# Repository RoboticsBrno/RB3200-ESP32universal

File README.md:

# RB3200 - ESP32 universal board

The ESP32 board you have always dreamed of by RobotikaBrno.cz!

## Features

- 4 pin headers for each of the ESP32-WROOM-32 pins
    - pin headers closest to the ESP32 module are directly exposed from the
      module
    - pin headers further from the module are protected by a serial 180R
      resistor - so you can attach e.g. a LED directly or you don't have to
      worry if you accidentally switch you grounded input to output.
    - each pin has its own 5V, 3V3 and GND pin
- Arduino Uno compatible headerincluded
- USB2Serial chip for easy button-less programming
- support for an external power supply with high-current voltage regulator
- diagnostic LEDs

## Populated board

## Manufacturing

There are pre-exported gerber files in the `gerbers` directory. This directory
is always up-to-date for every release (the master branch). There is also the
`bom.tsv` file which contains BOM with order codes for Farnell, TS, Mouser and
DigiKey. Note that the current development branch (`vX.Y`) does not guarantee
up-to-date gerber and BOM files.

As our board features many pin headers and you might not want to populate them
all, we did **not** include them in the BOM. Keep that please in mind when
ordering the components.

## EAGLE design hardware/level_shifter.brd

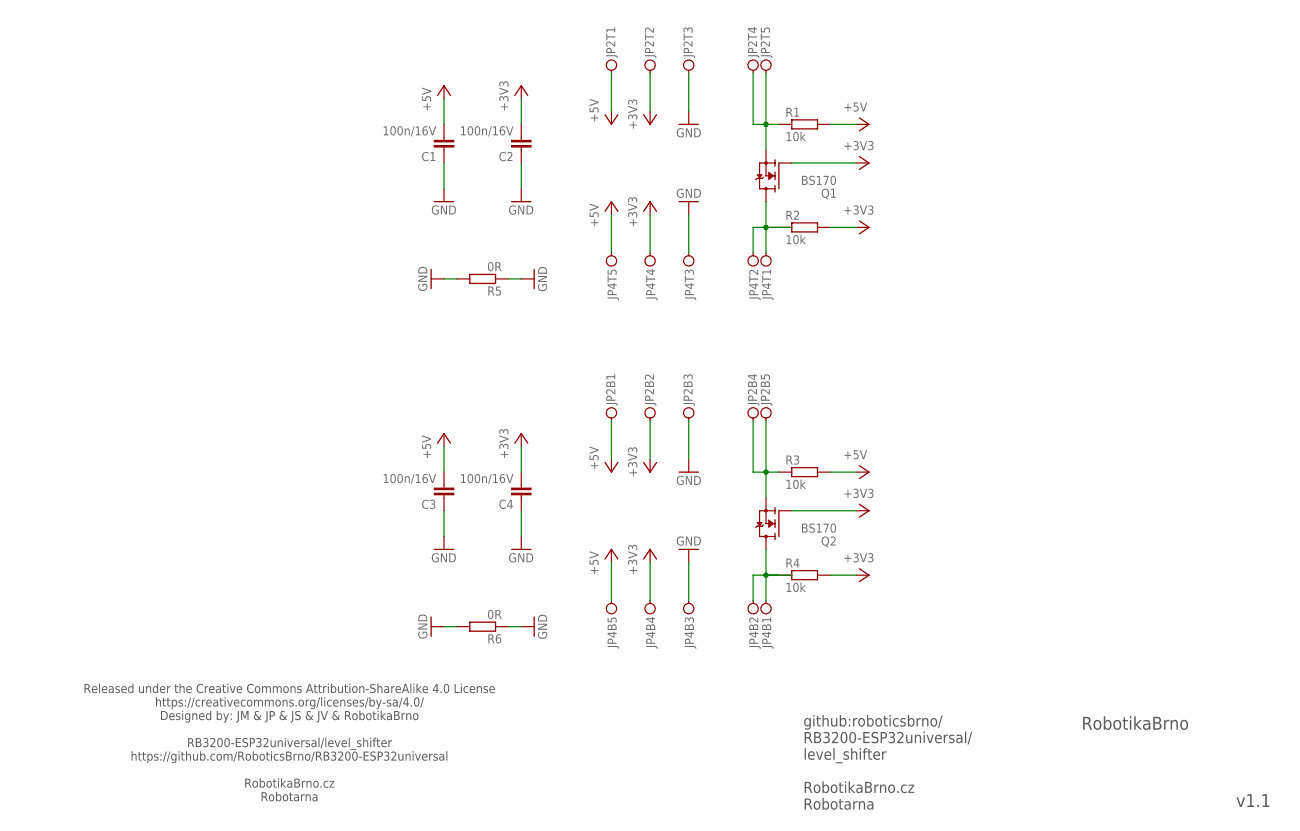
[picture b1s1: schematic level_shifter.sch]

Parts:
C1, C2, C3, C4: 100n/16V; C0603S
JP2, JP4: PINH2X05; PINH2X05SMD
Q1: BS170; SOT23_DIST
Q2: BS170; SOT23
R1, R2, R3, R4: 10k; R0603S
R5, R6: 0R; R1206S

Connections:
+3V3: C2.2, C4.2, JP2.B2, JP2.T2, JP4.B4, JP4.T4, Q1.1 (G), Q2.1 (G), R2.2, R4.2
+5V: C1.2, C3.2, JP2.B1, JP2.T1, JP4.B5, JP4.T5, R1.2, R3.2
GND: C1.1, C2.1, C3.1, C4.1, JP2.B3, JP2.T3, JP4.B3, JP4.T3, R5.1, R5.2, R6.1, R6.2
IN_B: JP4.B1, JP4.B2, Q2.3 (D), R4.1
IN_T: JP4.T1, JP4.T2, Q1.3 (D), R2.1
OUT_B: JP2.B4, JP2.B5, Q2.2 (S), R3.1
OUT_T: JP2.T4, JP2.T5, Q1.2 (S), R1.1

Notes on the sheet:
github:roboticsbrno/ RB3200-ESP32universal/ level_shifter RobotikaBrno.cz Robotarna
Released under the Creative Commons Attribution-ShareAlike 4.0 License https://creativecommons.org/licenses/by-sa/4.0/ Designed by: JM & JP & JS & JV & RobotikaBrno RB3200-ESP32universal/level_shifter https://github.com/RoboticsBrno/RB3200-ESP32universal RobotikaBrno.cz Robotarna
RobotikaBrno
v1.1

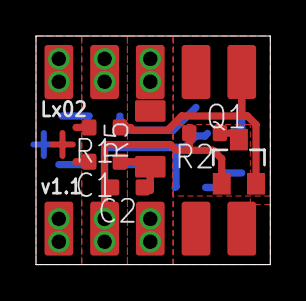
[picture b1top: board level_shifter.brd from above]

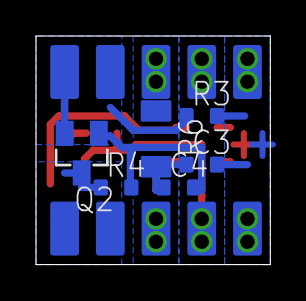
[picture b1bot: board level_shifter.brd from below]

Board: 2 copper layers, 13.0 x 12.7 mm, 14 parts (6 on the bottom side), 7 nets.

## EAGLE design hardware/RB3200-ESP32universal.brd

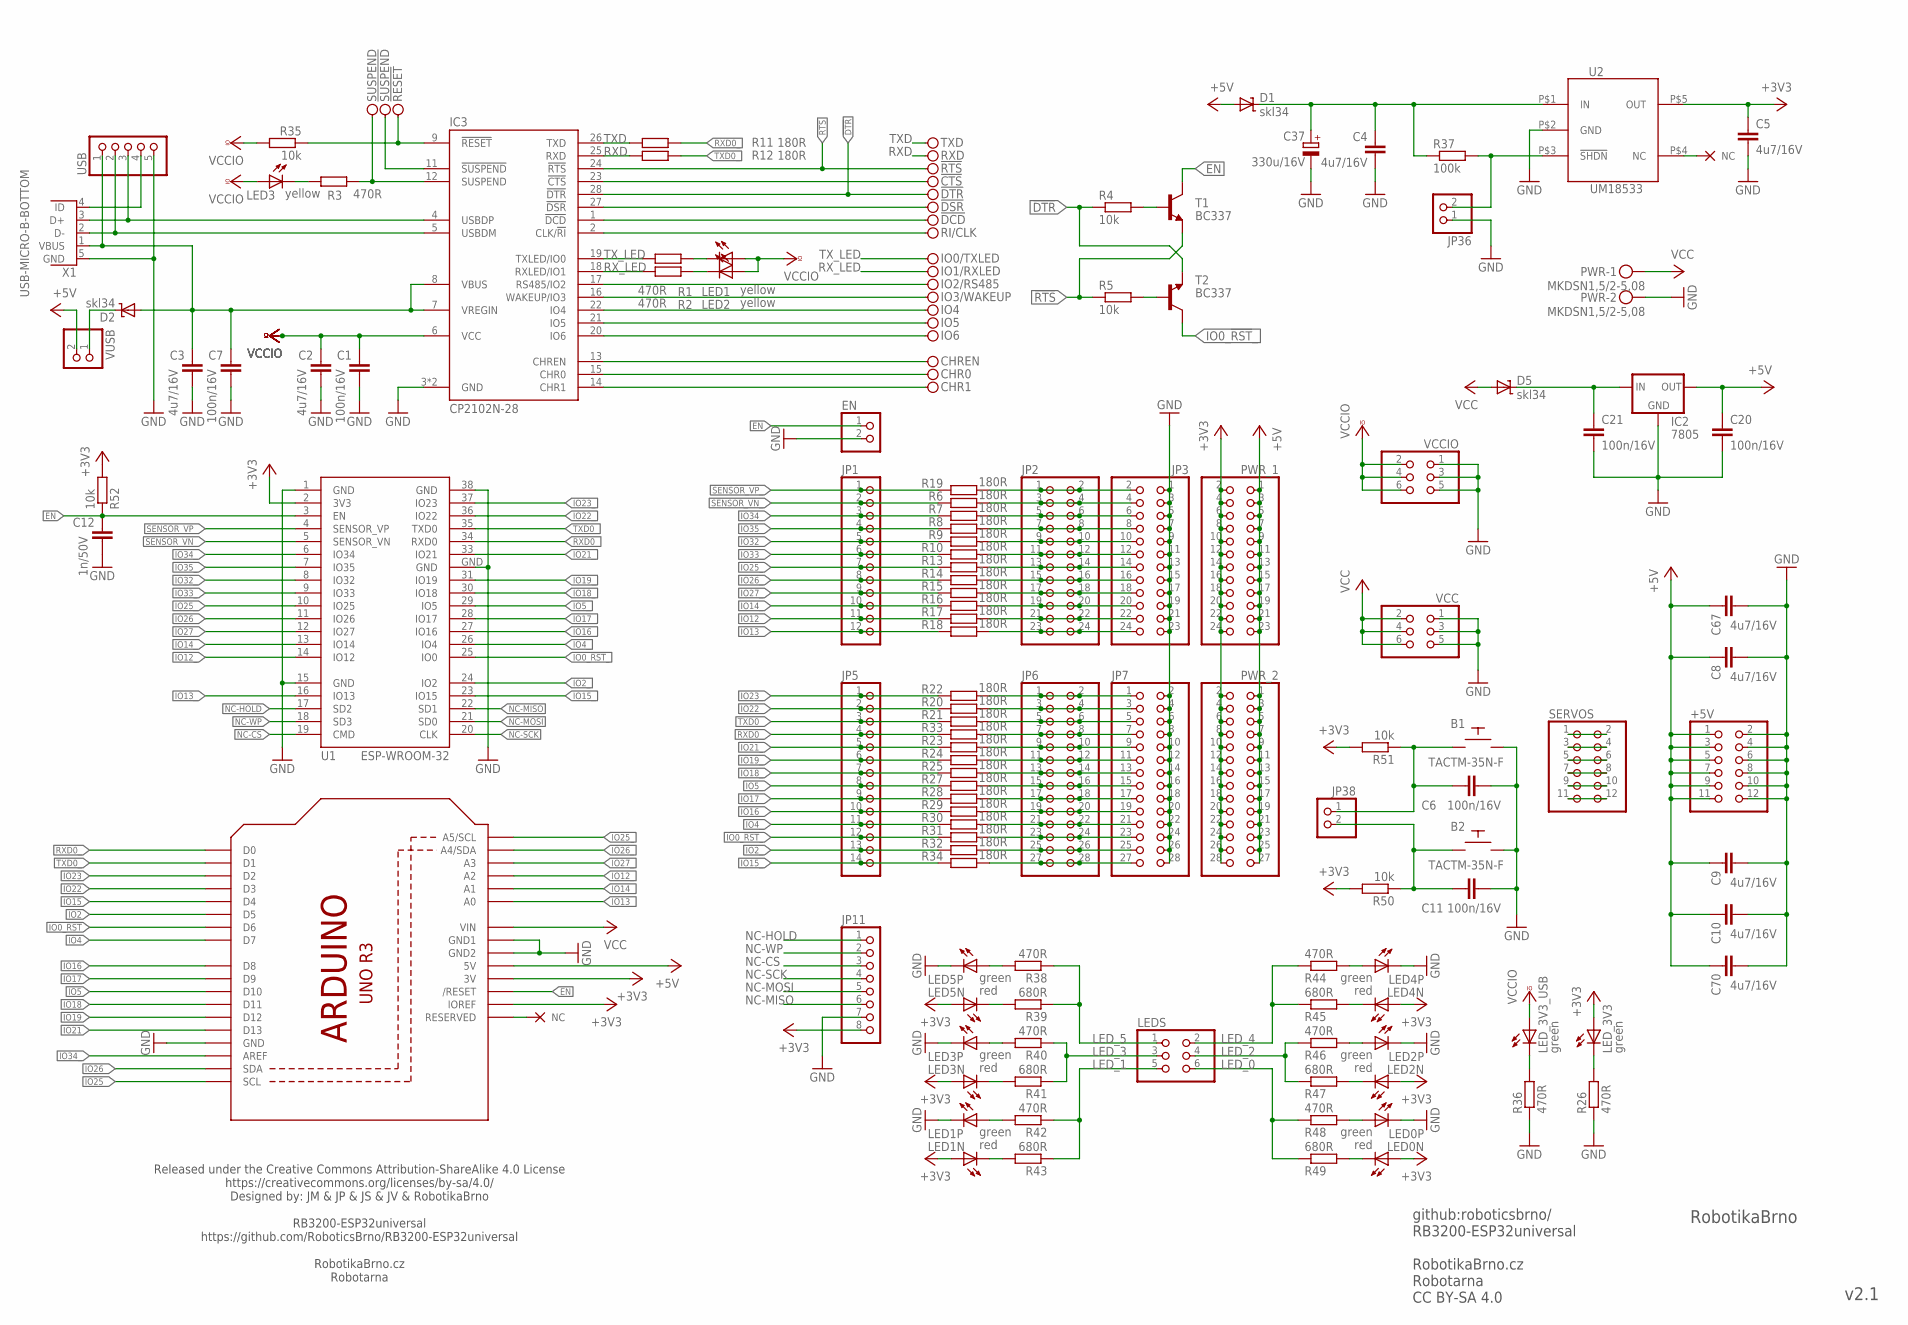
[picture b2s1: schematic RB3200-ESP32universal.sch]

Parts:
!CTS: PINH1X01; 1X01; DIGIKEY WM14724-ND
!DCD: PINH1X01; 1X01; DIGIKEY WM14724-ND
!DSR: PINH1X01; 1X01; DIGIKEY WM14724-ND
!DTR: PINH1X01; 1X01; DIGIKEY WM14724-ND
!RESET: PINH1X01; 1X01; DIGIKEY WM14724-ND
!RTS: PINH1X01; 1X01; DIGIKEY WM14724-ND
!SUSPEND: PINH1X01; 1X01; DIGIKEY WM14724-ND
+5V: PINHD-2X6; 2X06; DIGIKEY A122662-ND
B1, B2: TACTM-35N-F; DIGIKEY CKN1574TR-ND
C1, C6, C7, C11, C20, C21: 100n/16V; C0402; DIGIKEY 732-7478-1-ND
C2, C3, C4, C5: 4u7/16V; C0603; DIGIKEY 478-1253-1-ND
C8, C9, C10, C67, C70: 4u7/16V; C0805; DIGIKEY 1276-2970-1-ND
C12: 1n/50V; C0603; DIGIKEY 399-1082-1-ND
C37: 330u/16V; E5-10,5; DIGIKEY 493-6629-1-ND
CHR0, CHR1: PINH1X01; 1X01; DIGIKEY WM14724-ND
CHREN: PINH1X01; 1X01; DIGIKEY WM14724-ND
D1, D2, D5: skl34; SOD123
EN: PINHD-1X2; 1X02; DIGIKEY 3M9457-02-ND
IC2: 7805; 78XXS; DIGIKEY 1016-1538-5-ND
IC3: CP2102N-28; QFN28-PAD; MPN CP2102; DIGIKEY 336-3694-ND
IO0/TXLED, IO1/RXLED, IO2/RS485, IO3/WAKEUP, IO4, IO5, IO6: PINH1X01; 1X01; DIGIKEY WM14724-ND
JP1: PINHD-1X12; 1X12; DIGIKEY WM50014-12-ND
JP2, JP3: PINHD-2X12; 2X12; DIGIKEY WM8148-ND
JP5: PINHD-1X14; 1X14; FARNELL 2356164
JP6, JP7: PINHD-2X14; 2X14; DIGIKEY WM8150-ND
JP11: PINHD-1X8; 1X08; DIGIKEY A122911-ND
JP36, JP38: PINHD-1X2; 1X02; DIGIKEY 3M9457-02-ND
LED0N, LED1N, LED2N, LED3N, LED4N, LED5N: red; CHIPLED_0603; DIGIKEY 160-1447-1-ND
LED0P, LED1P, LED2P, LED3P, LED4P, LED5P: green; CHIPLED_0603; DIGIKEY 160-1446-1-ND
LED1, LED2, LED3: yellow; CHIP-LED0603; DIGIKEY 732-4981-1-ND
LEDS: PINHD-2X3; 2X03; DIGIKEY A122915-ND
LED_3V3, LED_3V3_USB: green; CHIPLED_0603; DIGIKEY 160-1446-1-ND
PWR: MKDSN1,5/2-5,08; DIGIKEY 277-5953-ND
PWR_1: PINHD-2X12; 2X12; DIGIKEY WM8148-ND
PWR_2: PINHD-2X14; 2X14; DIGIKEY WM8150-ND
R1, R2, R3, R26, R36, R38, R40, R42, R44, R46, R48: 470R; R0603; DIGIKEY 311-470HRCT-ND
R4, R5, R35, R50, R51, R52: 10k; R0603; DIGIKEY 311-10KGRCT-ND
R6, R7, R8, R9, R10, R11, R12, R13, R14, R15, R16, R17, R18, R19, R20, R21, R22, R23, R24, R25, R27, R28, R29, R30, R31, R32, R33, R34: 180R; R0603; DIGIKEY 311-180HRCT-ND
R37: 100k; R0603; DIGIKEY 311-100KHRCT-ND
R39, R41, R43, R45, R47, R49: 680R; R0603; DIGIKEY 311-680HRCT-ND
RI/CLK: PINH1X01; 1X01; DIGIKEY WM14724-ND
RXD: PINH1X01; 1X01; DIGIKEY WM14724-ND
SERVOS: PINHD-2X6; 2X06; DIGIKEY A122662-ND
SUSPEND: PINH1X01; 1X01; DIGIKEY WM14724-ND
T1, T2: BC337; SOT23; DIGIKEY 1727-2919-1-ND
TXD: PINH1X01; 1X01; DIGIKEY WM14724-ND
U1: ESP-WROOM-32; MPN ESP32-WROMM-32; DIGIKEY 1738-1294-ND
U2: UM18533; SOT23-5; MPN TPS73033DBVT; DIGIKEY 296-17580-1-ND
U3: ARDUINOR3-BPLACE
USB: PINHD-1X5; 1X05; DIGIKEY 732-5318-ND
VCC: PINHD-2X3; 2X03; DIGIKEY A122915-ND
VCCIO: PINHD-2X3; 2X03; DIGIKEY A122915-ND
VUSB: PINHD-1X2; 1X02; DIGIKEY 3M9457-02-ND
X1: USB-MICRO-B-BOTTOM; USB-MICRO-B-BOTTOM-MOLEX; DIGIKEY WM17141CT-ND

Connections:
3V3_IN: C4.1, C37.+, D1.C, R37.1, U2.P$1 (IN)
5V_USB: D2.C, VUSB.1
!DTR: !DTR.1, IC3.28 (!DTR), R4.1, T2.2 (E)
!DTR_B: R4.2, T1.1 (B)
!RESET: !RESET.1, IC3.9 (!RESET), R35.1
!RTS: !RTS.1, IC3.24 (!RTS), R5.1, T1.2 (E)
!RTS_B: R5.2, T2.1 (B)
!SHDN: JP36.2, R37.2, U2.P$3 (!SHDN)
!SUSPEND: !SUSPEND.1, IC3.11 (!SUSPEND)
+3V3: C5.1, JP11.8, LED0N.A, LED1N.A, LED2N.A, LED3N.A, LED4N.A, LED5N.A, LED_3V3.A, PWR_1.2, PWR_1.4, PWR_1.6, PWR_1.8, PWR_1.10, PWR_1.12, PWR_1.14, PWR_1.16, PWR_1.18, PWR_1.20, PWR_1.22, PWR_1.24, PWR_2.2, PWR_2.4, PWR_2.6, PWR_2.8, PWR_2.10, PWR_2.12, PWR_2.14, PWR_2.16, PWR_2.18, PWR_2.20, PWR_2.22, PWR_2.24, PWR_2.26, PWR_2.28, R50.2, R51.2, R52.2, U1.2 (3V3), U2.P$5 (OUT), U3.3V, U3.IOREF
+5V: +5V.1, +5V.3, +5V.5, +5V.7, +5V.9, +5V.11, C8.1, C9.1, C10.1, C20.1, C67.1, C70.1, D1.A, IC2.OUT, PWR_1.1, PWR_1.3, PWR_1.5, PWR_1.7, PWR_1.9, PWR_1.11, PWR_1.13, PWR_1.15, PWR_1.17, PWR_1.19, PWR_1.21, PWR_1.23, PWR_2.1, PWR_2.3, PWR_2.5, PWR_2.7, PWR_2.9, PWR_2.11, PWR_2.13, PWR_2.15, PWR_2.17, PWR_2.19, PWR_2.21, PWR_2.23, PWR_2.25, PWR_2.27, U3.5V, VUSB.2
BTN0: B1.P$4, C6.2, JP38.1, R51.1
BTN1: B2.P$4, C11.2, JP38.2, R50.1
CHR0: CHR0.1, IC3.15 (CHR0)
CHR1: CHR1.1, IC3.14 (CHR1)
CHREN: CHREN.1, IC3.13 (CHREN)
CLK/!RI: IC3.2 (CLK/!RI), RI/CLK.1
DCD: !DCD.1, IC3.1 (!DCD)
DM: IC3.5 (USBDM), USB.2, X1.2 (D-)
DP: IC3.4 (USBDP), USB.3, X1.3 (D+)
DSR: !DSR.1, IC3.27 (!DSR)
EN: C12.1, EN.1, R52.1, T1.3 (C), U1.3 (EN), U3.RESET (/RESET)
GND: +5V.2, +5V.4, +5V.6, +5V.8, +5V.10, +5V.12, B1.P$2, B2.P$2, C1.2, C2.2, C3.2, C4.2, C5.2, C6.1, C7.2, C8.2, C9.2, C10.2, C11.1, C12.2, C20.2, C21.2, C37.-, C67.2, C70.2, EN.2, IC2.GND, IC3.3 (GND), IC3.PAD (GND), JP3.1, JP3.3, JP3.5, JP3.7, JP3.9, JP3.11, JP3.13, JP3.15, JP3.17, JP3.19, JP3.21, JP3.23, JP7.2, JP7.4, JP7.6, JP7.8, JP7.10, JP7.12, JP7.14, JP7.16, JP7.18, JP7.20, JP7.22, JP7.24, JP7.26, JP7.28, JP11.7, JP36.1, LED0P.C, LED1P.C, LED2P.C, LED3P.C, LED4P.C, LED5P.C, PWR.2, R26.1, R36.1, U1.1 (GND), U1.15 (GND), U1.38 (GND), U1.GND, U2.P$2 (GND), U3.GND, U3.GND1, U3.GND2, USB.5, VCC.1, VCC.3, VCC.5, VCCIO.1, VCCIO.3, VCCIO.5, X1.5 (GND)
IO0_!RST: JP6.23, JP6.24, JP7.23, R31.1, U3.D6
IO0_!RST!_: JP5.12, R31.2, T2.3 (C), U1.25 (IO0)
IO2: JP6.25, JP6.26, JP7.25, R32.1, U3.D5
IO2_: JP5.13, R32.2, U1.24 (IO2)
IO4: JP6.21, JP6.22, JP7.21, R30.1, U3.D7
IO4_: JP5.11, R30.2, U1.26 (IO4)
IO5: JP6.15, JP6.16, JP7.15, R27.1, U3.D10
IO5_: JP5.8, R27.2, U1.29 (IO5)
IO12: JP2.21, JP2.22, JP3.22, R17.1
IO12_: JP1.11, R17.2, U1.14 (IO12), U3.A2
IO13: JP2.23, JP2.24, JP3.24, R18.1
IO13_: JP1.12, R18.2, U1.16 (IO13), U3.A0
IO14: JP2.19, JP2.20, JP3.20, R16.1
IO14_: JP1.10, R16.2, U1.13 (IO14), U3.A1
IO15: JP6.27, JP6.28, JP7.27, R34.1, U3.D4
IO15_: JP5.14, R34.2, U1.23 (IO15)
IO16: JP6.19, JP6.20, JP7.19, R29.1, U3.D8
IO16_: JP5.10, R29.2, U1.27 (IO16)
IO17: JP6.17, JP6.18, JP7.17, R28.1, U3.D9
IO17_: JP5.9, R28.2, U1.28 (IO17)
IO18: JP6.13, JP6.14, JP7.13, R25.1, U3.D11
IO18_: JP5.7, R25.2, U1.30 (IO18)
IO19: JP6.11, JP6.12, JP7.11, R24.1, U3.D12
IO19_: JP5.6, R24.2, U1.31 (IO19)
IO21: JP6.9, JP6.10, JP7.9, R23.1, U3.D13
IO21_: JP5.5, R23.2, U1.33 (IO21)
IO22: JP6.3, JP6.4, JP7.3, R20.1, U3.D3
IO22_: JP5.2, R20.2, U1.36 (IO22)
IO23: JP6.1, JP6.2, JP7.1, R22.1, U3.D2
IO23_: JP5.1, R22.2, U1.37 (IO23)
IO25: JP2.13, JP2.14, JP3.14, R13.1
IO25_: JP1.7, R13.2, U1.10 (IO25), U3.A5 (A5/SCL), U3.SCL
IO26: JP2.15, JP2.16, JP3.16, R14.1
IO26_: JP1.8, R14.2, U1.11 (IO26), U3.A4 (A4/SDA), U3.SDA
IO27: JP2.17, JP2.18, JP3.18, R15.1
IO27_: JP1.9, R15.2, U1.12 (IO27), U3.A3
IO32: JP2.9, JP2.10, JP3.10, R9.1
IO32_: JP1.5, R9.2, U1.8 (IO32)
IO33: JP2.11, JP2.12, JP3.12, R10.1
IO33_: JP1.6, R10.2, U1.9 (IO33)
IO34: JP2.5, JP2.6, JP3.6, R7.1
IO34_: JP1.3, R7.2, U1.6 (IO34), U3.AREF
IO35: JP2.7, JP2.8, JP3.8, R8.1
IO35_: JP1.4, R8.2, U1.7 (IO35)
LED0N: LED0N.C, R49.2
LED0P: LED0P.A, R48.2
LED1N: LED1N.C, R43.2
LED1P: LED1P.A, R42.2
LED2N: LED2N.C, R47.2
LED2P: LED2P.A, R46.2
LED3N: LED3N.C, R41.2
LED3P: LED3P.A, R40.2
LED4N: LED4N.C, R45.2
LED4P: LED4P.A, R44.2
LED5N: LED5N.C, R39.2
LED5P: LED5P.A, R38.2
LED_0: LEDS.6, R48.1, R49.1
LED_1: LEDS.5, R42.1, R43.1
LED_2: LEDS.4, R46.1, R47.1
LED_3: LEDS.3, R40.1, R41.1
LED_3V3: LED_3V3.C, R26.2
LED_3V3_USB: LED_3V3_USB.C, R36.2
LED_4: LEDS.2, R44.1, R45.1
LED_5: LEDS.1, R38.1, R39.1
unnamed: !CTS.1, IC3.23 (!CTS)
unnamed: LED3.C, R3.2
unnamed: SERVOS.1, SERVOS.2
unnamed: SERVOS.3, SERVOS.4
unnamed: SERVOS.5, SERVOS.6
unnamed: SERVOS.7, SERVOS.8
unnamed: SERVOS.9, SERVOS.10
unnamed: SERVOS.11, SERVOS.12
NC-CS: JP11.3, U1.19 (CMD)
NC-HOLD: JP11.1, U1.17 (SD2)
NC-MISO: JP11.6, U1.22 (SD1)
NC-MOSI: JP11.5, U1.21 (SD0)
NC-SCK: JP11.4, U1.20 (CLK)
NC-WP: JP11.2, U1.18 (SD3)
RX-LED: LED2.C, R2.1
RXD: IC3.25 (RXD), R12.1, RXD.1
RXD0: JP6.7, JP6.8, JP7.7, R33.1, U3.D0
RXD0_: JP5.4, R11.2, R33.2, U1.34 (RXD0)
RX_LED: IC3.18 (RXLED/IO1), IO1/RXLED.1, R2.2
SENSOR_VN: JP2.3, JP2.4, JP3.4, R6.1
SENSOR_VN_: JP1.2, R6.2, U1.5 (SENSOR_VN)
SENSOR_VP: JP2.1, JP2.2, JP3.2, R19.1
SENSOR_VP_: JP1.1, R19.2, U1.4 (SENSOR_VP)
SUSPEND: IC3.12 (SUSPEND), R3.1, SUSPEND.1
TX-LED: LED1.C, R1.1
TXD: IC3.26 (TXD), R11.1, TXD.1
TXD0: JP6.5, JP6.6, JP7.5, R21.1, U3.D1
TXD0_: JP5.3, R12.2, R21.2, U1.35 (TXD0)
TX_LED: IC3.19 (TXLED/IO0), IO0/TXLED.1, R1.2
U2_NC: U2.P$4 (NC)
USBID: USB.4, X1.4 (ID)
USBIO3_RS485: IC3.17 (RS485/IO2), IO2/RS485.1
USBIO3_WAKEUP: IC3.16 (WAKEUP/IO3), IO3/WAKEUP.1
USBIO4: IC3.22 (IO4), IO4.1
USBIO5: IC3.21 (IO5), IO5.1
USBIO6: IC3.20 (IO6), IO6.1
VCC: D5.A, PWR.1, VCC.2, VCC.4, VCC.6
VCC->5V: C21.1, D5.C, IC2.IN
VCCIO: C1.1, C2.1, IC3.6 (VCC), LED1.A, LED2.A, LED3.A, LED_3V3_USB.A, R35.2, VCCIO.2, VCCIO.4, VCCIO.6
VUSB: C3.1, C7.1, D2.A, IC3.7 (VREGIN), IC3.8 (VBUS), USB.1, X1.1 (VBUS)

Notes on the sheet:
github:roboticsbrno/ RB3200-ESP32universal RobotikaBrno.cz Robotarna CC BY-SA 4.0
RobotikaBrno
v2.1
Released under the Creative Commons Attribution-ShareAlike 4.0 License https://creativecommons.org/licenses/by-sa/4.0/ Designed by: JM & JP & JS & JV & RobotikaBrno RB3200-ESP32universal https://github.com/RoboticsBrno/RB3200-ESP32universal RobotikaBrno.cz Robotarna

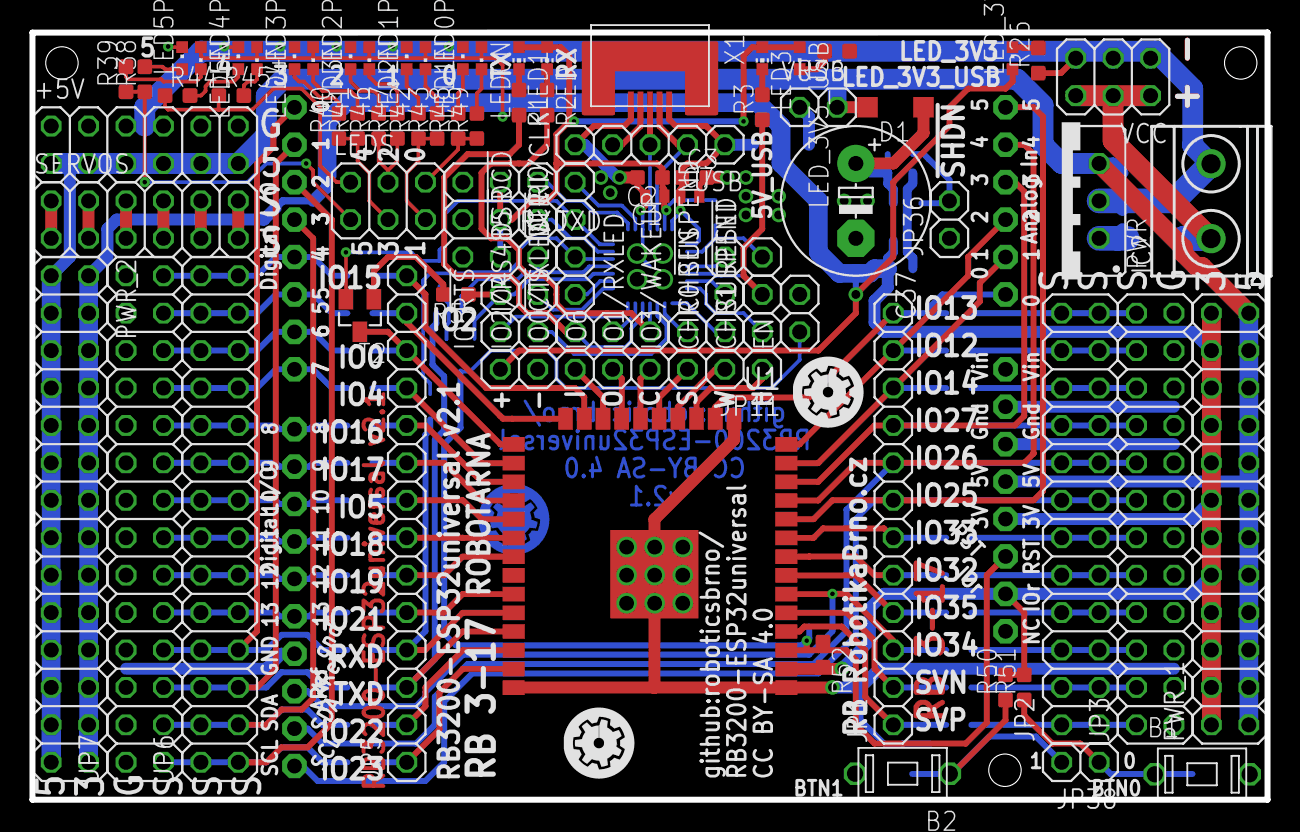
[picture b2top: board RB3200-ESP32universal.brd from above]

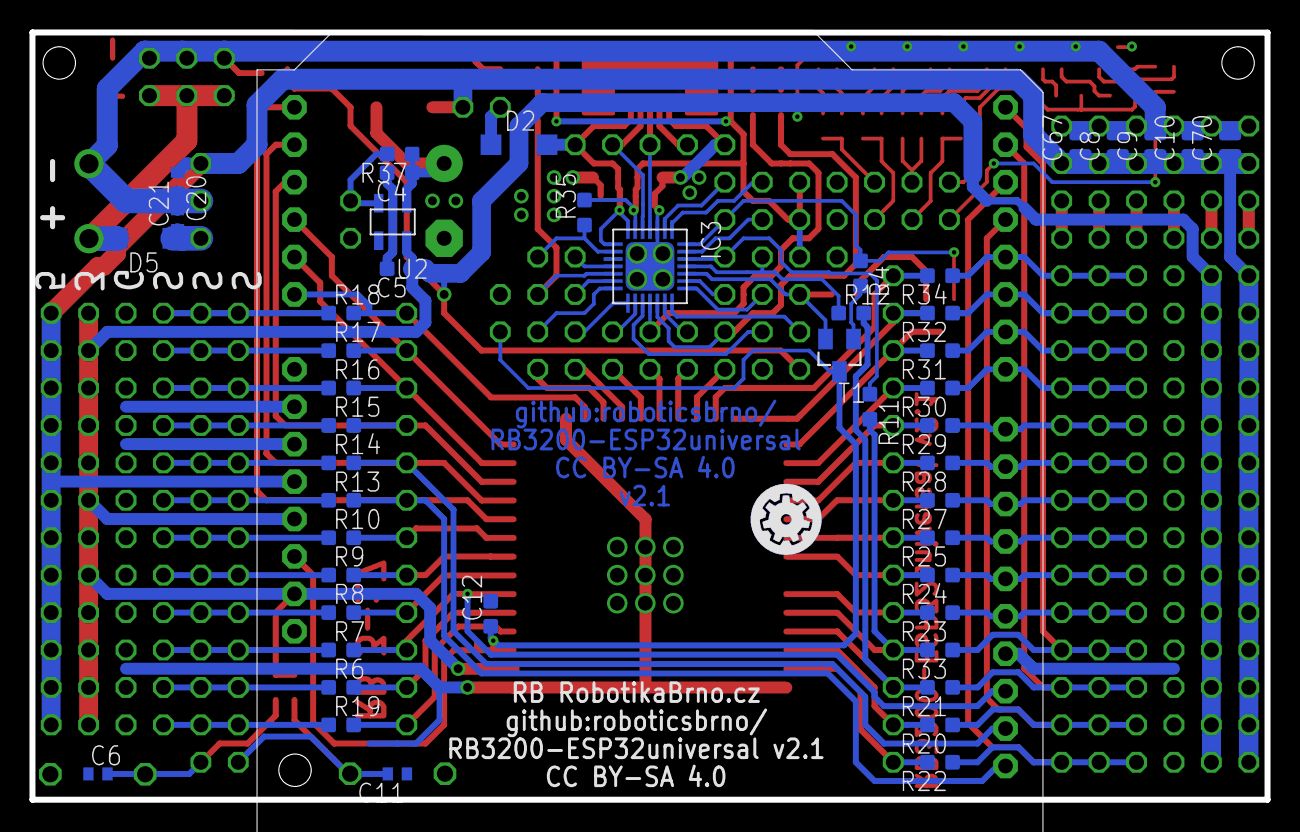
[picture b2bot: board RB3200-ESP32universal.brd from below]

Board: 2 copper layers, 83.8 x 52.1 mm, 140 parts (48 on the bottom side), 126 nets.

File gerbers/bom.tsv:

Qty	Value	Device	Package	Parts	Description	DIGIKEY	FARNELL	MANUFACTURER	MOUSER	MPN	RS
1		PINHD-1X12	1X12	JP1	PIN HEADER
1		PINHD-1X14	1X14	JP5	PIN HEADER
4		PINHD-1X2	1X02	EN, JP36, JP38, VUSB	PIN HEADER
1		PINHD-1X5	1X05	USB	PIN HEADER
1		PINHD-1X8	1X08	JP11	PIN HEADER
3		PINHD-2X12	2X12	JP2, JP3, PWR_1	PIN HEADER
3		PINHD-2X14	2X14	JP6, JP7, PWR_2	PIN HEADER
3		PINHD-2X3	2X03	LEDS, VCC, VCCIO	PIN HEADER
2		PINHD-2X6	2X06	+5V, SERVOS	PIN HEADER
1	100k	R-EU_R0603	R0603	R37	RESISTOR, European symbol	311-100KHRCT-ND	9238727		603-RC0603FR-07100KL		566-787
6	100n/16V	C-EUC0402	C0402	C1, C6, C7, C11, C20, C21	CAPACITOR, European symbol	732-7478-1-ND	2533923		710-885012105001		788-2871
6	10k	R-EU_R0603	R0603	R4, R5, R35, R50, R51, R52	RESISTOR, European symbol	311-10KGRCT-ND	9238603		603-RC0603FR-0710KL		213-2418
28	180R	R-EU_R0603	R0603	R6, R7, R8, R9, R10, R11, R12, R13, R14, R15, R16, R17, R18, R19, R20, R21, R22, R23, R24, R25, R27, R28, R29, R30, R31, R32, R33, R34	RESISTOR, European symbol	311-180HRCT-ND	9238395		603-RC0603FR-07180RL		566-412
1	1n/50V	C-EUC0603	C0603	C12	CAPACITOR, European symbol	399-1082-1-ND	1414608		80-C0603C102K5R		264-4551
1	330u/16V	CPOL-EUE5-10.5	E5-10,5	C37	POLARIZED CAPACITOR, European symbol	493-6629-1-ND	9692045		140-REA331M1CBK0811P		707-5840
11	470R	R-EU_R0603	R0603	R1, R2, R3, R26, R36, R38, R40, R42, R44, R46, R48	RESISTOR, European symbol	311-470HRCT-ND	9238441		603-RC0603FR-07470RL		566-547
4	4u7/16V	C-EUC0603	C0603	C2, C3, C4, C5	CAPACITOR, European symbol	478-1253-1-ND	9227784		06034D475KAT2A		698-3248
5	4u7/16V	C-EUC0805	C0805	C8, C9, C10, C67, C70	CAPACITOR, European symbol	1276-2970-1-ND	2320854		963-EMK212B7475KG-T		766-1037
6	680R	R-EU_R0603	R0603	R39, R41, R43, R45, R47, R49	RESISTOR, European symbol	311-680HRCT-ND	9238468		603-RC0603FR-13680RL
1	7805	78XXS	78XXS	IC2	VOLTAGE REGULATOR	1016-1538-5-ND	9756078		701-SP7805V-L		769-5466
1	ARDUINOR3-BPLACE	ARDUINOR3-BPLACE	ARDUINOR3-BPLACE	U3	This is a new object for the new Arduino R3 - with extra pins that you may want to use (such as IOref, and duplicated A4/A5
2	BC337	NPN-SOT23-BEC	SOT23	T1, T2		1727-2919-1-ND	1081224		771-BC817-40-T/R		216-9410
1	CP2102N-28	CP2102N-28	QFN28-PAD	IC3		336-3694-ND	2577279	Silicon Labs	634-CP2102NA01GQFN28	CP2102	526-8841
1	ESP-WROOM-32	ESP-WROOM-32	ESP-WROOM-32	U1	Espressif Systems ESP-WROOM-32	1738-1294-ND		Espressif Systems		ESP32-WROMM-32
1	MKDSN1,5/2-5,08	MKDSN1,5/2-5,08	MKDSN1,5/2-5,08	PWR	MKDSN 1,5/ 2-5,08 Printklemme	277-5953-ND	2490945		651-1890963		804-5118
21	PINH1X01	PINH1X01	1X01	!CTS, !DCD, !DSR, !DTR, !RESET, !RTS, !SUSPEND, CHR0, CHR1, CHREN, IO0/TXLED, IO1/RXLED, IO2/RS485, IO3/WAKEUP, IO4, IO5, IO6, RI/CLK, RXD, SUSPEND, TXD
2	TACTM-35N-F	TACTM-35N-F	TACTM-35N-F	B1, B2		CKN1574TR-ND	2079520		611-PTS635SL43SMTRLF		135-9609
1	UM18533	UM185XX	SOT23-5	U2		296-17580-1-ND	1135395	Texas Instruments	595-TPS73033DBVR	TPS73033DBVT	620-1401
1	USB-MICRO-B-BOTTOM	USB-MICRO-B-BOTTOM	USB-MICRO-B-BOTTOM-MOLEX	X1		WM17141CT-ND	1568026		538-47346-0001		702-5475
8	green	LEDCHIPLED_0603	CHIPLED_0603	LED0P, LED1P, LED2P, LED3P, LED4P, LED5P, LED_3V3, LED_3V3_USB	LED	160-1446-1-ND	2293494		859-LTST-C191KGKT		872-1799
6	red	LEDCHIPLED_0603	CHIPLED_0603	LED0N, LED1N, LED2N, LED3N, LED4N, LED5N	LED	160-1447-1-ND	2322071		859-LTST-C191KRKT		127-8415
3	skl34	SHOTTKY-SOD123	SOD123	D1, D2, D5
3	yellow	LEDCHIP-LED0603	CHIP-LED0603	LED1, LED2, LED3	LED	732-4981-1-ND	2322074		710-150060YS75000		815-4219

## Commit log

2017-04-07 Init repo
2017-04-07 Publish version 1.0
2017-04-07 Add information text about license and authors
2017-04-07 Add license file for hardware and .gitignore for Eagle temporary files
2017-04-30 Publish version 2.0 of RB3200-ESP32universal and level_shifter DPS
2017-04-30 updated silkscreen (and added bSilk)
2017-04-30 shrunk level_shifter by one signal pinhead
2017-05-01 outline of C37 in horizontal position moved to layer reference
2017-05-02 Make pin header pads octagonal
2017-05-02 Move labels to layer 21
    Allows for easy KiCAD import.
2017-05-25 Add enable pullup
    This solves board flashing issues.
2017-05-25 Change EN pullup value to simplify BOM
2017-05-25 Add support for Kitnic
2017-05-25 Add gerbers for Kitnic
2017-05-27 Add order codes to the components.
2017-05-27 Add MPM to the BOM
2017-05-27 Add unit info into the gerber drill file
2017-05-27 Improve BOM a bit, optimise for low MOQ
2017-05-28 Tweak BOM according to #4
2017-05-28 Remove order codes for pin headers from BOM, add readme note
2017-05-29 Update labels in SilkScreen (tPlace)
2017-05-29 level_shifter: repair one polygon and add license to schema
2021-10-08 Rename and update kitspace.yaml

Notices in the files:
parts and their libraries:
esp32: Creative Commons Attribution-ShareAlike 4.0 International
